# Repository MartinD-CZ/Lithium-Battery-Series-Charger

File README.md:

# Lithium Battery Series Charger

*a board that allows you to charge multiple lithium cells in series and also provides protection and balancing
*see the article [here](http://embedblog.eu/?p=123)!*

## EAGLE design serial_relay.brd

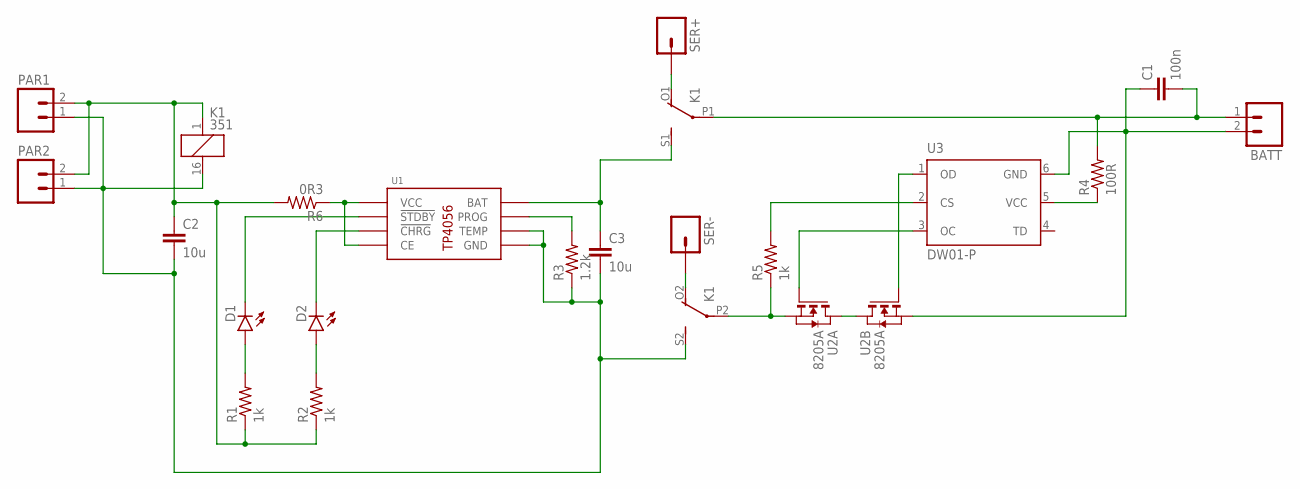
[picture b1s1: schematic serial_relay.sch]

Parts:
BATT: M02PTH3; 1X02_LONGPADS
C1: 100n; 1206
C2, C3: 10u; 1206
D1, D2: LED1206; LED-1206
K1: 351
PAR1, PAR2: M02PTH3; 1X02_LONGPADS
R1, R2, R5: 1k; 1206
R3: 1.2k; 1206
R4: 100R; 1206
R6: 0R3; 1206
SER+: M01PTH_LONGPAD; 1X01_LONGPAD
SER-: M01PTH_LONGPAD; 1X01_LONGPAD
U1: TP4056; SOP8
U2: 8205A; TSSOP8
U3: DW01-P; SOT23-6L

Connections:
unnamed: K1.P2, R5.1, U2.2 (S), U2.3 (S)
unnamed: K1.O1 (O), SER+.1
unnamed: K1.O2 (O), SER-.1
unnamed: D1.A, R1.2
unnamed: D1.C, U1.6 (!STDBY)
unnamed: R4.1, U3.5 (VCC)
unnamed: D2.A, R2.2
unnamed: BATT.2, C1.1, U2.6 (S), U2.7 (S), U3.6 (GND)
unnamed: U2.1 (D), U2.8 (D)
unnamed: U2.5 (G), U3.1 (OD)
unnamed: U2.4 (G), U3.3 (OC)
unnamed: D2.C, U1.7 (!CHRG)
unnamed: R5.2, U3.2 (CS)
unnamed: R3.2, U1.2 (PROG)
unnamed: R6.1, U1.4 (VCC), U1.8 (CE)
unnamed: C2.1, K1.1, PAR1.2, PAR2.2, R1.1, R2.1, R6.2
unnamed: C2.2, C3.2, K1.16 (2), K1.S2 (S), PAR1.1, PAR2.1, R3.1, U1.1 (TEMP), U1.3 (GND)
V+: BATT.1, C1.2, K1.P1, R4.2
V_BATT: C3.1, K1.S1 (S), U1.5 (BAT)

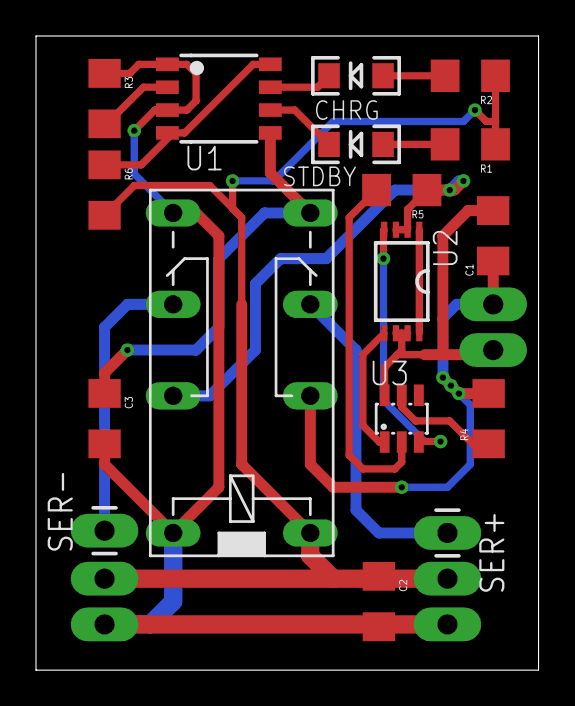
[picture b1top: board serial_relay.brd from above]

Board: 2 copper layers, 27.9 x 35.2 mm, 20 parts (0 on the bottom side), 19 nets.

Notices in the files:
parts and their libraries:
SparkFun-Connectors: Licensing: Creative Commons ShareAlike 4.0 International - https://creativecommons.org/licenses/by-sa/4.0
